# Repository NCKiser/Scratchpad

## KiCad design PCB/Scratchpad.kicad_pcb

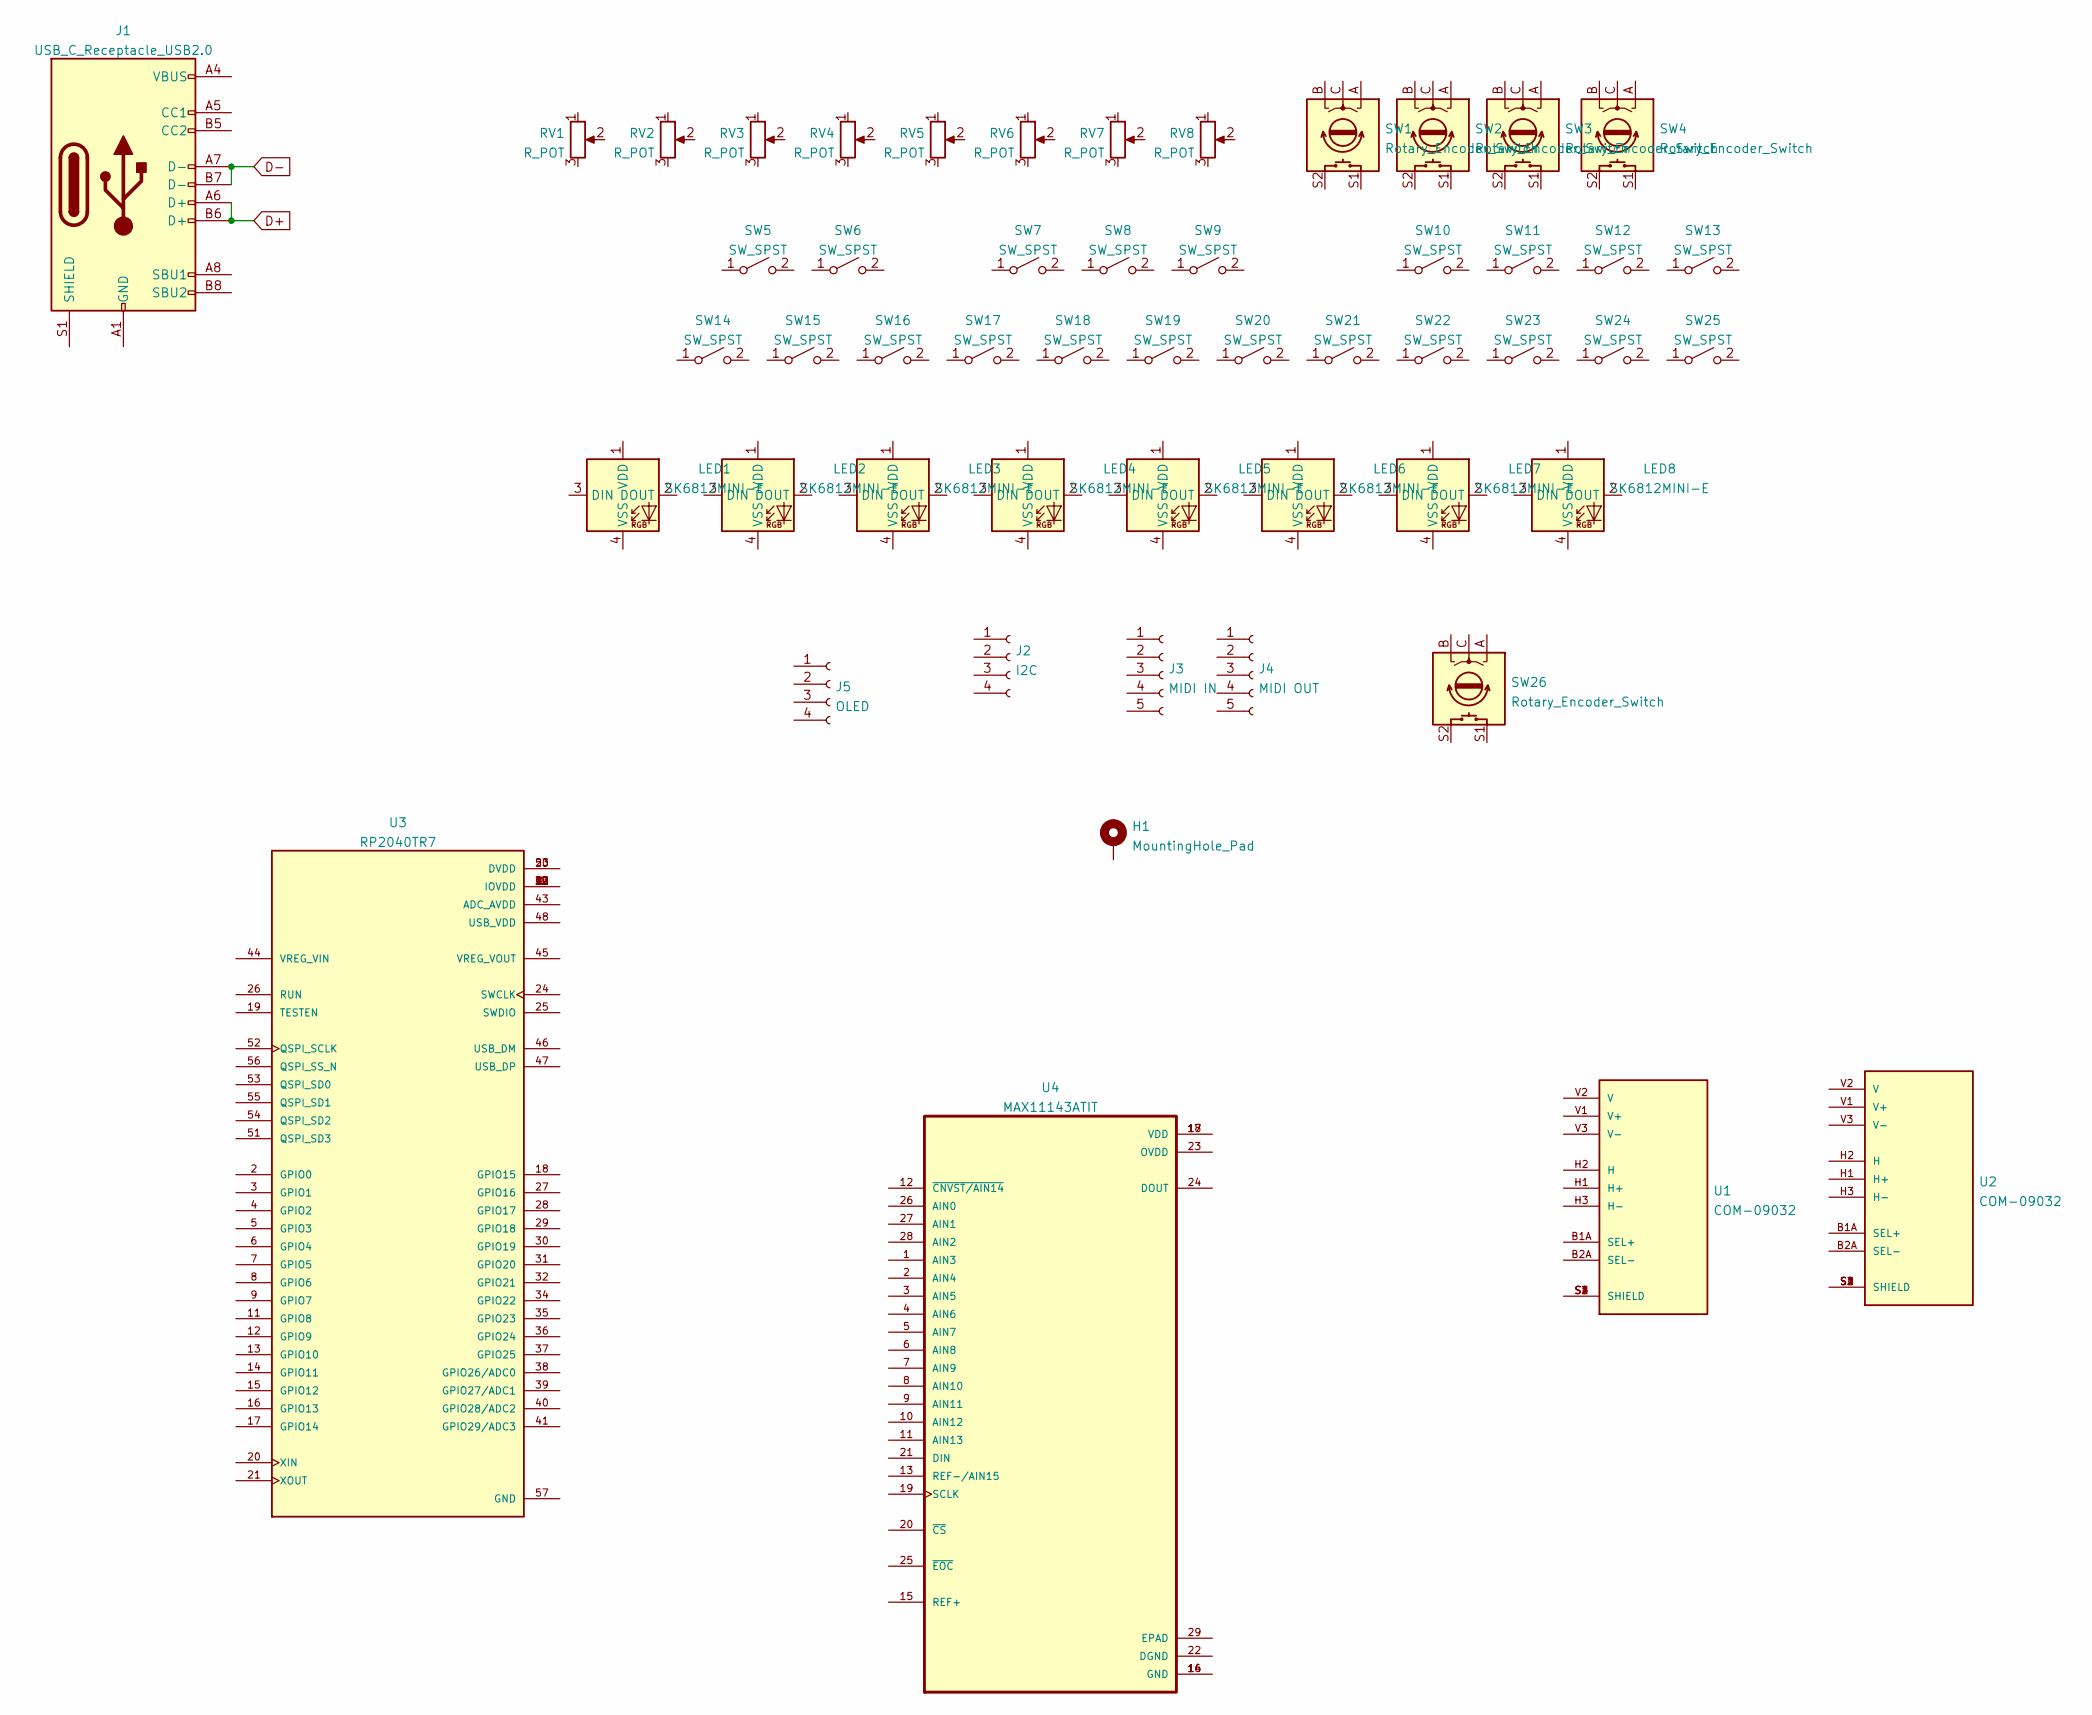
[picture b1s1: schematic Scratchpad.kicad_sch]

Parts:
H1: MountingHole_Pad; Minivan-reference
J1: USB_C_Receptacle_USB2.0; USB_C_Receptacle_HRO_TYPE-C-31-M-12
J2: I2C; PinSocket_1x04_P2.54mm_Vertical
J3: MIDI IN; TRRS_Jack
J4: MIDI OUT; TRRS_Jack
J5: OLED; PinHeader_1x04_P2.54mm_Vertical
LED1, LED2, LED3, LED4, LED5, LED6, LED7, LED8: SK6812MINI-E; LED_MX_6028R
RV1, RV2, RV3, RV4, RV5, RV6, RV7, RV8: R_POT; Potentiometer_Bourns_PTA2043_Single_Slide
SW1, SW2, SW3, SW4, SW26: Rotary_Encoder_Switch; RotaryEncoder_Alps_EC11E-Switch_Vertical_H20mm
SW5, SW6, SW7, SW8, SW9, SW10, SW11, SW12, SW13, SW14, SW15, SW16, SW17, SW18, SW19, SW20, SW21, SW22, SW23, SW24, SW25: SW_SPST; SW_MX_HS_1u
U1, U2: COM-09032; XDCR_COM-09032; PARTREV N/A
U3: RP2040TR7; QFN40P700X700X90-57N; PARTREV 1.7.1
U4: MAX11143ATIT; QFN50P500X500X80-29N

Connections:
D+: J1.A6 (D+), J1.B6 (D+)
D-: J1.A7 (D-), J1.B7 (D-)
unnamed: J1.A1 (GND), J1.A12 (GND), J1.B1 (GND), J1.B12 (GND)
unnamed: J1.A4 (VBUS), J1.A9 (VBUS), J1.B4 (VBUS), J1.B9 (VBUS)
unnamed: U1.S1 (SHIELD), U1.S2 (SHIELD), U1.S3 (SHIELD), U1.S4 (SHIELD)
unnamed: U2.S1 (SHIELD), U2.S2 (SHIELD), U2.S3 (SHIELD), U2.S4 (SHIELD)
unnamed: U3.1 (IOVDD), U3.10 (IOVDD), U3.22 (IOVDD), U3.33 (IOVDD), U3.42 (IOVDD), U3.49 (IOVDD)
unnamed: U3.23 (DVDD), U3.50 (DVDD)
unnamed: U4.14 (GND), U4.16 (GND)
unnamed: U4.17 (VDD), U4.18 (VDD)

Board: 2 copper layers, 52 parts (37 on the bottom side), 10 nets, no tracks yet.

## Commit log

2022-03-09 Added some components, I2C is pin header now
2022-04-13 Some footprint updates
2022-11-08 some changes
